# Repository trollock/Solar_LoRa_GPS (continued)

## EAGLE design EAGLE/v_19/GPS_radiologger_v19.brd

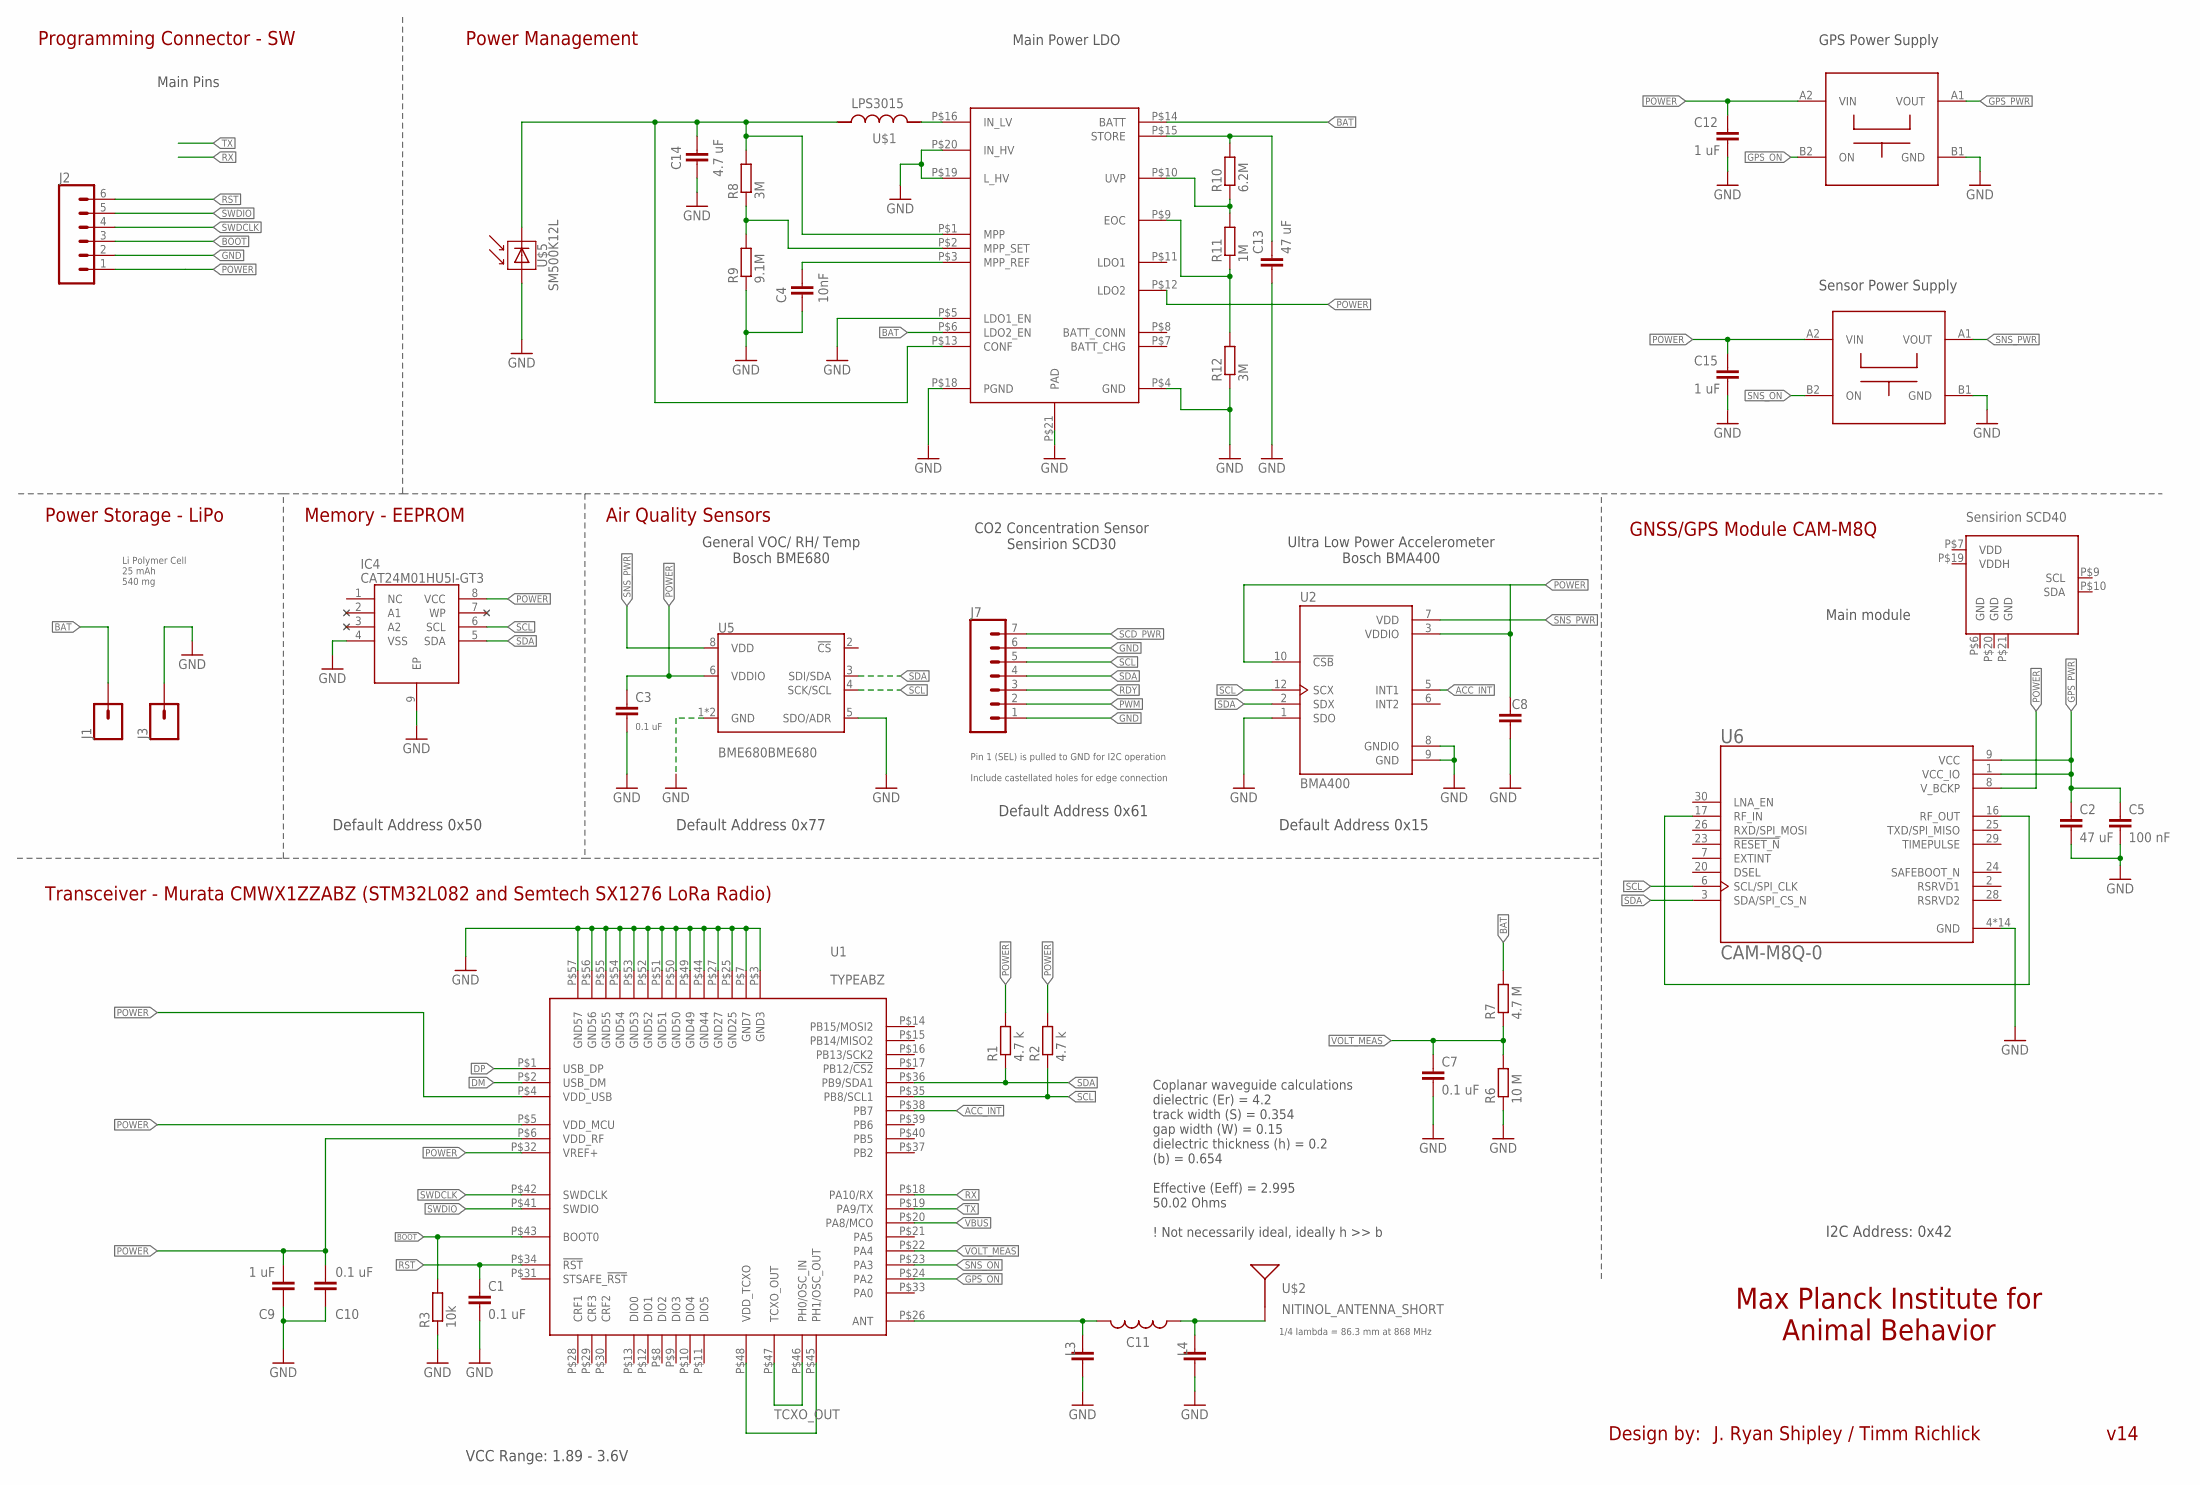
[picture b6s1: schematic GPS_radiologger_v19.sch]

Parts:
C1, C3, C7, C10: 0.1 uF; C0201
C2: 47 uF; C0201
C4: 10nF; C0201
C5: 100 nF; C0201
C8: C-EUC0201; C0201
C9, C12, C15: 1 uF; C0201
C11: 0.1uF; L0201
C13: 47 uF; C0805K
C14: 4.7 uF; C0201
IC4: CAT24M01HU5I-GT3; SON50P300X200X55-9N
J1, J3: CONN_01PTH_NO_SILK_YES_STOP; 1X01_NO_SILK
J2: CONN_06NO_SILK_NO_POP; 1X06_NO_SILK
J7: CONN_07NO_SILK; 1X07_NO_SILK
L3, L4: C-EUC0201; C0201
R1, R2: 4.7 k; R0201
R3: 10k; R0201
R6: 10 M; R0201
R7: 4.7 M; R0201
R8, R12: 3M; R0201
R9: 9.1M; R0201
R10: 6.2M; R0201
R11: 1M; R0201
U1: TYPEABZ
U2: BMA400; XDCR_BMA400
U4: SPV1050
U5: BME680BME680; LGA3.0X3.0
U6: CAM-M8Q-0; LCC100P960X1400X210-31N
U$1: LPS3015; LPS_3015
U$2: NITINOL_ANTENNA_SHORT; ICARUS_NITINOL_ANTENNA_SHORT
U$3, U$4: TPS22916CL; YFP0004-DSBGA
U$5: SM500K12L
U$6: SCD40; SCD40_LGA

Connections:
ACC_INT: U1.P$38 (PB7), U2.5 (INT1)
BAT: J1.1, R7.2, U4.P$6 (LDO2_EN), U4.P$14 (BATT)
BOOT: J2.3, R3.2, U1.P$43 (BOOT0)
DM: U1.P$2 (USB_DM)
DP: U1.P$1 (USB_DP)
GND: C1.2, C2.2, C3.2, C4.2, C5.2, C7.2, C8.2, C9.1, C10.1, C12.2, C13.2, C14.2, C15.2, IC4.4 (VSS), IC4.9 (EP), J2.2, J3.1, J7.1, J7.6, L3.2, L4.2, R3.1, R6.1, R9.1, R12.1, U1.P$3 (GND3), U1.P$7 (GND7), U1.P$25 (GND25), U1.P$27 (GND27), U1.P$44 (GND44), U1.P$49 (GND49), U1.P$50 (GND50), U1.P$51 (GND51), U1.P$52 (GND52), U1.P$53 (GND53), U1.P$54 (GND54), U1.P$55 (GND55), U1.P$56 (GND56), U1.P$57 (GND57), U2.1 (SDO), U2.8 (GNDIO), U2.9 (GND), U4.P$4 (GND), U4.P$5 (LDO1_EN), U4.P$18 (PGND), U4.P$19 (L_HV), U4.P$20 (IN_HV), U4.P$21 (PAD), U5.1 (GND), U5.5 (SDO/ADR), U5.7 (GND), U6.4 (GND), U6.5 (GND), U6.10 (GND), U6.11 (GND), U6.12 (GND), U6.13 (GND), U6.14 (GND), U6.15 (GND), U6.18 (GND), U6.19 (GND), U6.21 (GND), U6.22 (GND), U6.27 (GND), U6.31 (GND), U$3.B1 (GND), U$4.B1 (GND), U$5.P$2 (MINUS)
GPS_ON: U1.P$24 (PA2), U$3.B2 (ON)
GPS_PWR: C2.1, C5.1, U6.1 (VCC_IO), U6.9 (VCC), U$3.A1 (VOUT)
unnamed: U1.P$45 (PH1/OSC_OUT), U1.P$48 (VDD_TCXO)
unnamed: C11.2, L3.1, U1.P$26 (ANT)
unnamed: U4.P$16 (IN_LV), U$1.P$2 (2)
unnamed: C8.1, U2.3 (VDDIO)
unnamed: R8.1, R9.2, U4.P$2 (MPP_SET)
unnamed: C14.1, R8.2, U4.P$1 (MPP), U4.P$13 (CONF), U$1.P$1 (1), U$5.P$1 (PLUS)
unnamed: R10.1, R11.2, U4.P$10 (UVP)
unnamed: R11.1, R12.2, U4.P$9 (EOC)
unnamed: C11.1, L4.1, U$2.1, U$2.2, U$2.3
unnamed: C13.1, R10.2, U4.P$15 (STORE)
unnamed: C4.1, U4.P$3 (MPP_REF)
unnamed: U6.16 (RF_OUT), U6.17 (RF_IN)
POWER: C3.1, C9.2, C10.2, C12.1, C15.1, IC4.8 (VCC), J2.1, R1.2, R2.2, U1.P$4 (VDD_USB), U1.P$5 (VDD_MCU), U1.P$6 (VDD_RF), U1.P$32 (VREF+), U2.10 (!CSB), U4.P$12 (LDO2), U5.6 (VDDIO), U6.8 (V_BCKP), U$3.A2 (VIN), U$4.A2 (VIN)
PWM: J7.2
RDY: J7.3
RST: C1.1, J2.6, U1.P$34 (!RST)
RX: U1.P$18 (PA10/RX)
SCD_PWR: J7.7
SCL: IC4.6 (SCL), J7.5, R2.1, U1.P$35 (PB8/SCL1), U2.12 (SCX), U5.4 (SCK/SCL), U6.6 (SCL/SPI_CLK)
SDA: IC4.5 (SDA), J7.4, R1.1, U1.P$36 (PB9/SDA1), U2.2 (SDX), U5.3 (SDI/SDA), U6.3 (SDA/SPI_CS_N)
SNS_ON: U1.P$23 (PA3), U$4.B2 (ON)
SNS_PWR: U2.7 (VDD), U5.8 (VDD), U$4.A1 (VOUT)
SWDCLK: J2.4, U1.P$42 (SWDCLK)
SWDIO: J2.5, U1.P$41 (SWDIO)
TCXO_OUT: U1.P$46 (PH0/OSC_IN), U1.P$47 (TCXO_OUT)
TX: U1.P$19 (PA9/TX)
VBUS: U1.P$20 (PA8/MCO)
VOLT_MEAS: C7.1, R6.2, R7.1, U1.P$22 (PA4)

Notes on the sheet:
GNSS/GPS Module CAM-M8Q
VCC Range: 1.89 - 3.6V
I2C Address: 0x42
Max Planck Institute for Animal Behavior
Transceiver - Murata CMWX1ZZABZ (STM32L082 and Semtech SX1276 LoRa Radio)
Programming Connector - SW
Power Storage - LiPo
Design by:
J. Ryan Shipley / Timm Richlick
v14
Li Polymer Cell 25 mAh 540 mg
Power Management
Main Power LDO
Air Quality Sensors
Memory - EEPROM
GPS Power Supply
Main module
Coplanar waveguide calculations dielectric (Er) = 4.2 track width (S) = 0.354 gap width (W) = 0.15 dielectric thickness (h) = 0.2 (b) = 0.654 Effective (Eeff) = 2.995 50.02 Ohms ! Not necessarily ideal, ideally h >> b
Sensor Power Supply
Main Pins
Default Address 0x77
Default Address 0x50
1/4 lambda = 86.3 mm at 868 MHz
General VOC/ RH/ Temp Bosch BME680
Ultra Low Power Accelerometer Bosch BMA400
Default Address 0x15
CO2 Concentration Sensor Sensirion SCD30
Pin 1 (SEL) is pulled to GND for I2C operation
Include castellated holes for edge connection
Default Address 0x61

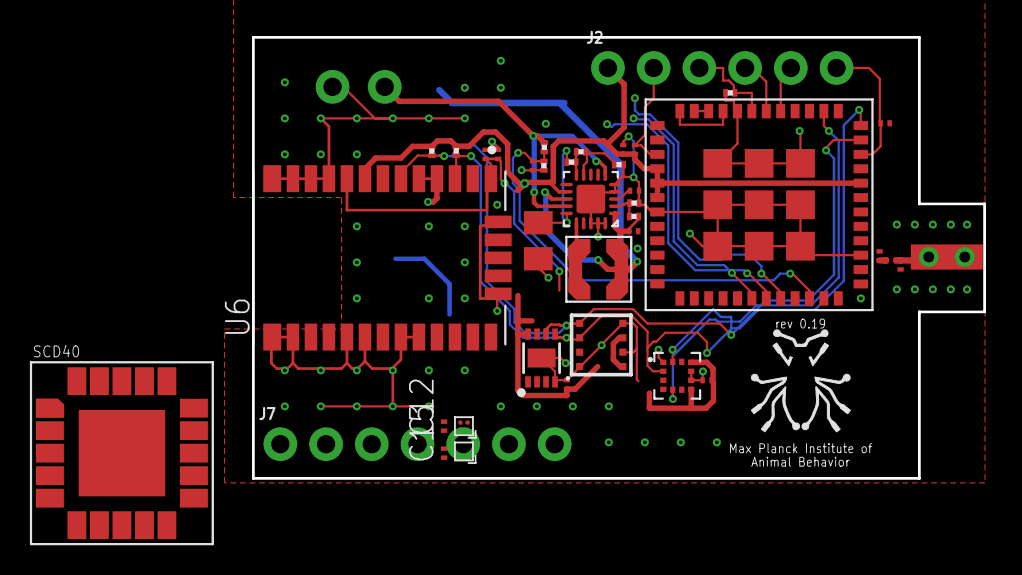
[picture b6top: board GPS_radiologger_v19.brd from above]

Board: 2 copper layers, 40.6 x 24.5 mm, 42 parts (1 on the bottom side), 28 nets.

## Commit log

2019-11-04 added v3
2019-11-05 more_pcb_edits
2019-11-22 Commit new state diagram illustrations
2019-12-12 moar edits
    revision 3 to main board layout, inclusion of TPL5110, possible future exchange for RV-3028
2020-06-16 recent changes / update since being idle
2020-06-17 rolling along with v14 / implementation of solar power
2020-06-17 Create CMWX_LoRa_GPS_v14 4.s#1
2020-06-19 latest edits v14
2020-07-22 recent general edits
2020-09-10 recent board updates
2020-11-18 recent updates
    recent updates
2020-12-24 typical updates
    recent changes, updates to v19
2020-12-30 recent updates
    added basic *.ino file for tag testing
2020-12-30 testing eeprom and adding structured classes for all sub modules
2023-01-23 v27_updates
    recent updates with some hardware changes, switch from L70-M39B to LG77L Quectel GPS modules
